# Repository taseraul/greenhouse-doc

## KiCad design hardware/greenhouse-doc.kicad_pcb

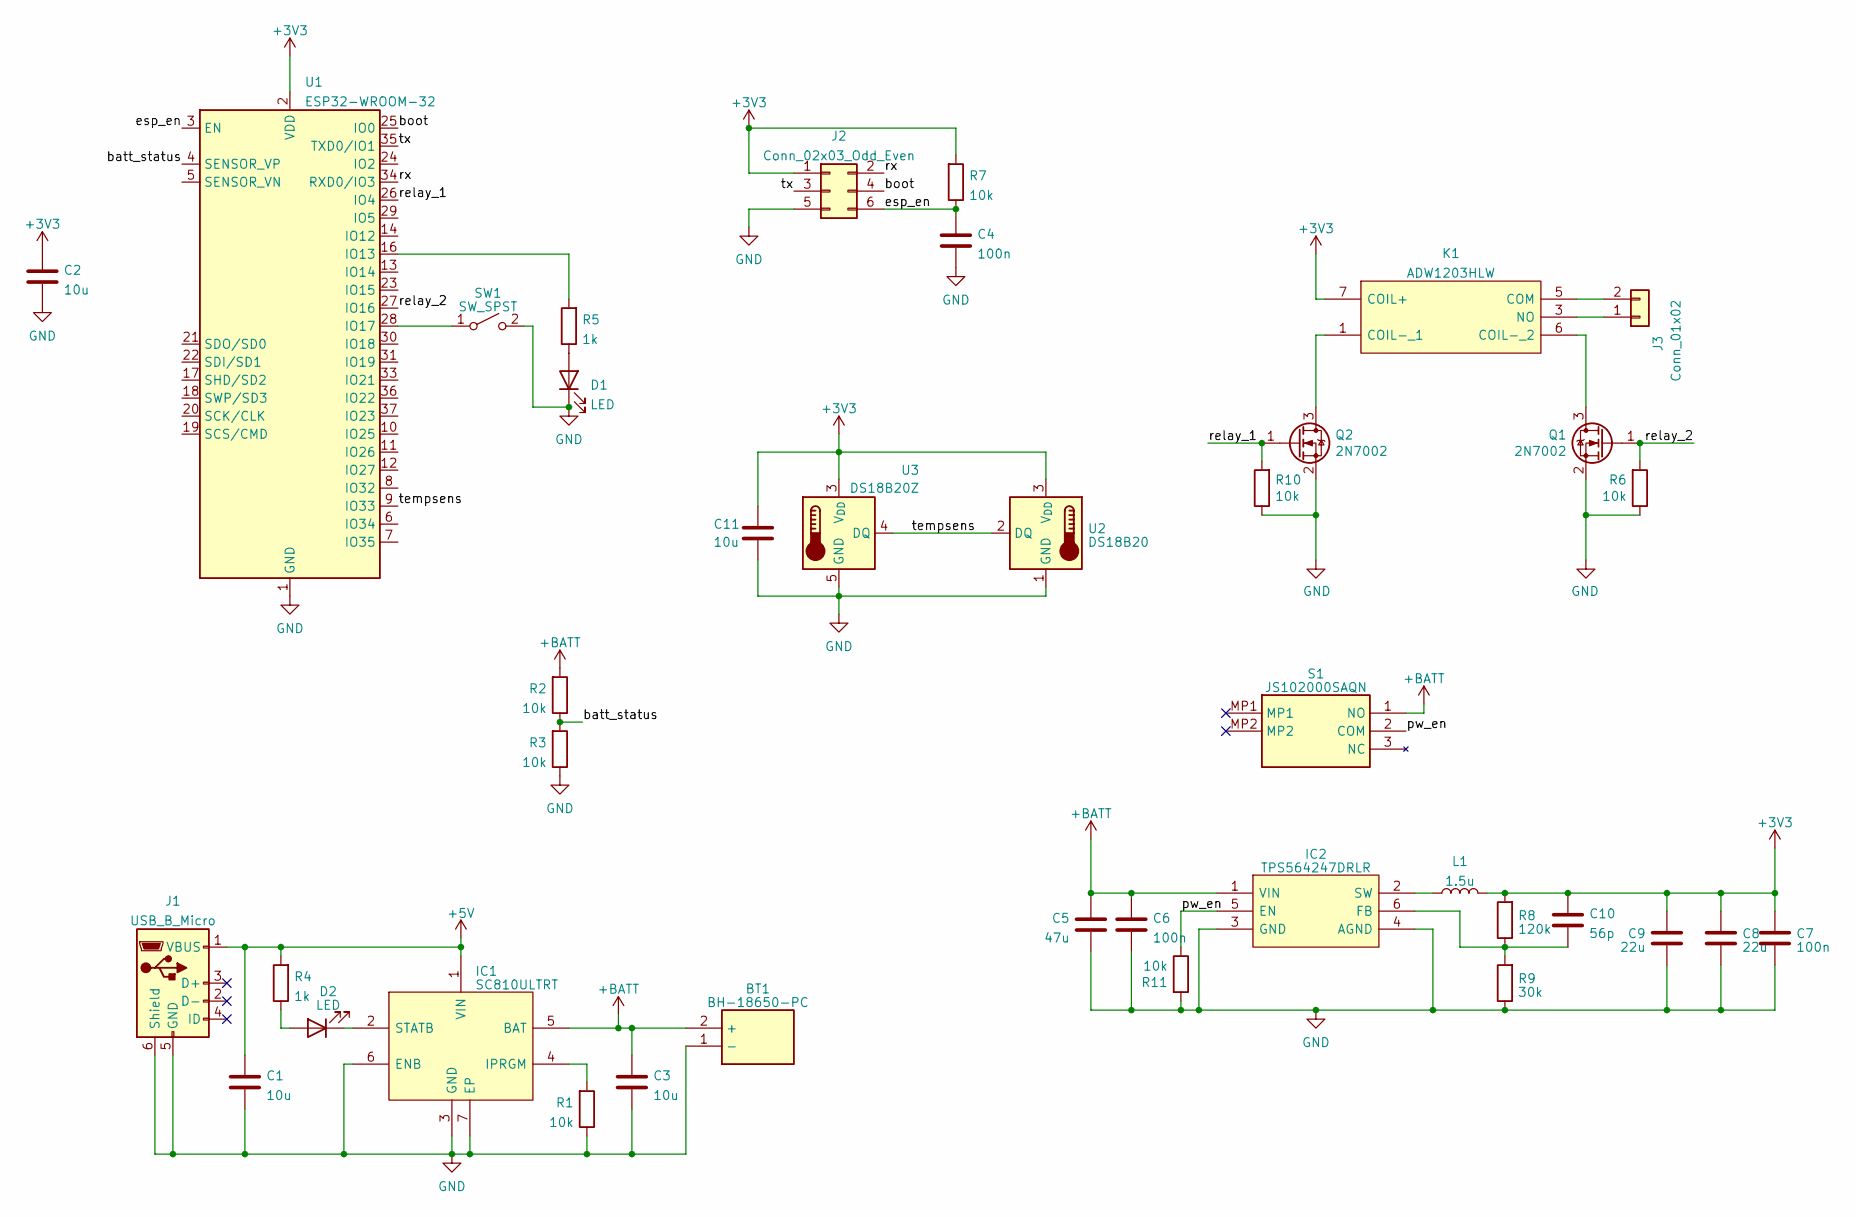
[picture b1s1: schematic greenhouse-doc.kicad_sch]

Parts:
BT1: BH-18650-PC; BH18650PC; Manufacturer_Part_Number BH-18650-PC
C1, C2, C3, C11: 10u; C_0805_2012Metric
C4, C6, C7: 100n; C_0805_2012Metric
C5: 47u; C_0805_2012Metric
C8, C9: 22u; C_0805_2012Metric
C10: 56p; C_0805_2012Metric
D1, D2: LED; LED_0805_2012Metric
IC1: SC810ULTRT; SON50P200X200X60-7N-D; Mouser Part Number 947-SC810ULTRT
IC2: TPS564247DRLR; SOT50P160X60-6N; Mouser Part Number 595-TPS564247DRLR
J1: USB_B_Micro; USB_Micro-B_Molex-105017-0001
J2: Conn_02x03_Odd_Even; PinHeader_2x03_P2.54mm_Vertical
J3: Conn_01x02; TerminalBlock_Phoenix_MKDS-1,5-2_1x02_P5.00mm_Horizontal
K1: ADW1203HLW; Mouser Part Number 769-ADW1203HLW
L1: 1.5u; L_Wuerth_MAPI-4020
Q1, Q2: 2N7002; SOT-23
R1, R2, R3, R6, R7, R10, R11: 10k; R_0805_2012Metric
R4, R5: 1k; R_0805_2012Metric
R8: 120k; R_0805_2012Metric
R9: 30k; R_0805_2012Metric
S1: JS102000SAQN; Mouser Part Number 611-JS102000SAQN
SW1: SW_SPST; SW_Tactile_SPST_Angled_PTS645Vx58-2LFS
U1: ESP32-WROOM-32
U2: DS18B20; TO-92_Inline
U3: DS18B20Z; SOIC-8_3.9x4.9mm_P1.27mm

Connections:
+3V3: C2.1, C7.1, C8.1, C9.1, C10.1, C11.1, J2.1, K1.7 (COIL+), L1.1, R7.2, R8.2, U1.2 (VDD), U2.3 (V_{DD}), U3.3 (V_{DD})
+5V: C1.1, IC1.1 (VIN), J1.1 (VBUS), R4.2
+BATT: BT1.2 (+), C3.1, C5.1, C6.1, IC1.5 (BAT), IC2.1 (VIN), R2.2, S1.1 (NO)
/batt_status: R2.1, R3.2, U1.4 (SENSOR_VP)
/boot: J2.4, U1.25 (IO0)
/esp_en: C4.1, J2.6, R7.1, U1.3 (EN)
/pw_en: IC2.5 (EN), R11.1, S1.2 (COM)
/relay_1: Q2.1 (G), R10.2, U1.26 (IO4)
/relay_2: Q1.1 (G), R6.2, U1.27 (IO16)
/rx: J2.2, U1.34 (RXD0/IO3)
/tempsens: U1.9 (IO33), U2.2 (DQ), U3.4 (DQ)
/tx: J2.3, U1.35 (TXD0/IO1)
GND: BT1.1 (-), C1.2, C2.2, C3.2, C4.2, C5.2, C6.2, C7.2, C8.2, C9.2, C11.2, D1.1 (K), IC1.3 (GND), IC1.6 (ENB), IC1.7 (EP), IC2.3 (GND), IC2.4 (AGND), J1.5 (GND), J1.6 (Shield), J2.5, Q1.2 (S), Q2.2 (S), R1.1, R3.1, R6.1, R9.1, R10.1, R11.2, SW1.2 (B), U1.1 (GND), U1.15 (GND), U1.38 (GND), U1.39 (GND), U2.1 (GND), U3.5 (GND)
unnamed: D1.2 (A), R5.1
unnamed: D2.2 (A), R4.1
unnamed: D2.1 (K), IC1.2 (STATB)
unnamed: IC1.4 (IPRGM), R1.2
unnamed: C10.2, IC2.6 (FB), R8.1, R9.2
unnamed: IC2.2 (SW), L1.2
unnamed: J3.1, K1.3 (NO)
unnamed: J3.2, K1.5 (COM)
unnamed: K1.1 (COIL-_1), Q2.3 (D)
unnamed: K1.6 (COIL-_2), Q1.3 (D)
unnamed: SW1.1 (A), U1.28 (IO17)
unnamed: R5.2, U1.16 (IO13)

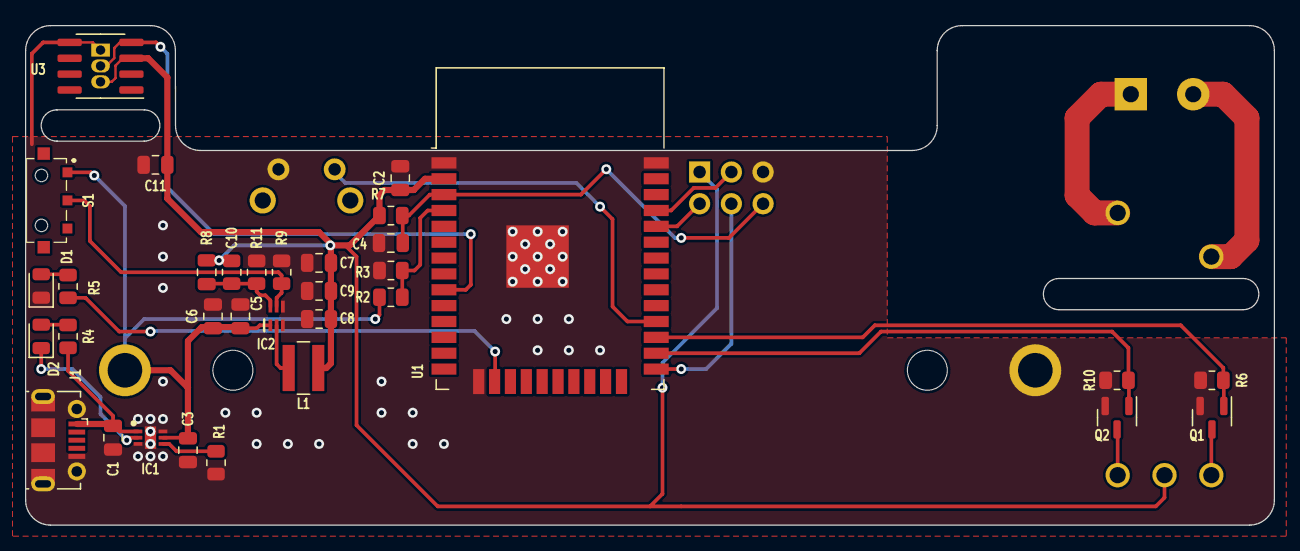
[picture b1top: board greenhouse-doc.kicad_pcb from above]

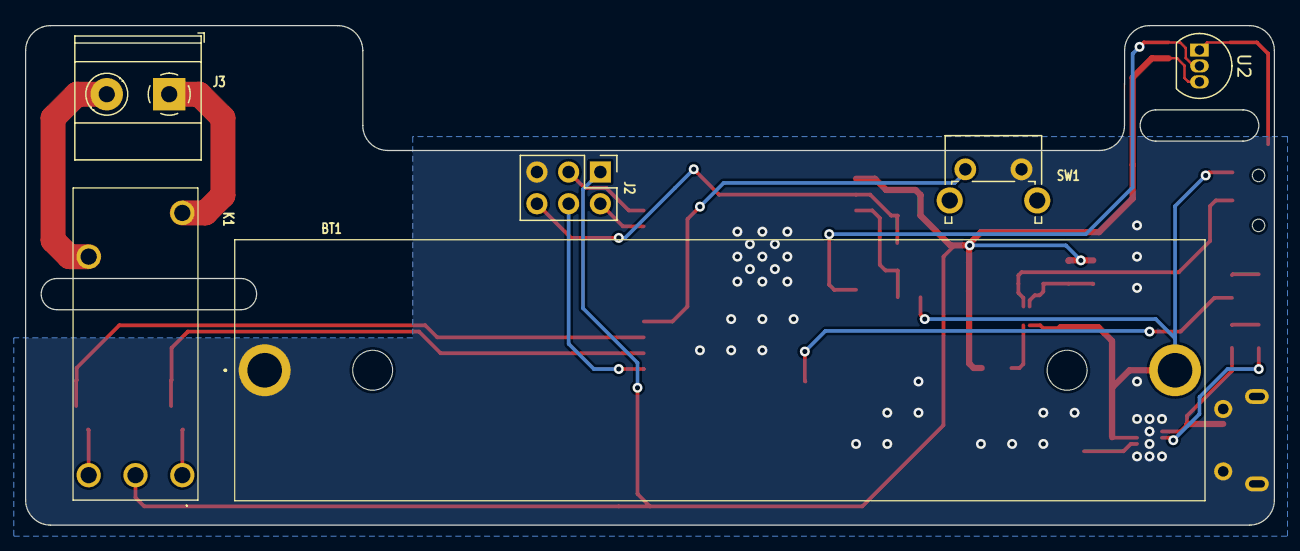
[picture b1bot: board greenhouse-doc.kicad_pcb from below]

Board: 2 copper layers, 100.0 x 40.0 mm, 39 parts (6 on the bottom side), 25 nets.

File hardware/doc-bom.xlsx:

Comment | Designator | Footprint | JLCPCB Part #（optional）
DS18B20 | U2 | TO-92_Inline
10k | R6,R7,R2,R10,R1,R11,R3 | R_0805_2012Metric | C17414
10u | C3,C2,C1,C11 | C_0805_2012Metric | C15850
JS102000SAQN | S1 | JS102000SAQN
DS18B20Z | U3 | SOIC-8_3.9x4.9mm_P1.27mm | C695837
30k | R9 | R_0805_2012Metric | C17621
1.5u | L1 | L_Wuerth_MAPI-4020 | C135238
100n | C4,C6,C7 | C_0805_2012Metric | C49678
120k | R8 | R_0805_2012Metric | C17436
47u | C5 | C_0805_2012Metric | C16780
TPS564247DRLR | IC2 | SOT50P160X60-6N
2N7002 | Q1,Q2 | SOT-23 | C8545
USB_B_Micro | J1 | USB_Micro-B_Molex-105017-0001 | C136000
ESP32-WROOM-32 | U1 | ESP32-WROOM-32 | C82899
56p | C10 | C_0805_2012Metric | C39148
SC810ULTRT | IC1 | SON50P200X200X60-7N-D
LED | D2,D1 | LED_0805_2012Metric | C2296
22u | C8,C9 | C_0805_2012Metric | C59461
1k | R5,R4 | R_0805_2012Metric | C17513
BH-18650-PC | BT1 | BH18650PC
Conn_01x02 | J3 | TerminalBlock_Phoenix_MKDS-1,5-2_1x02_P5.00mm_Horizontal
ADW1203HLW | K1 | ADW1203HLW | C963496
SW_SPST | SW1 | SW_Tactile_SPST_Angled_PTS645Vx58-2LFS
Conn_02x03_Odd_Even | J2 | PinHeader_2x03_P2.54mm_Vertical

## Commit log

2023-12-26 v2 hardware
2024-01-27 multi-user multi-device new database
